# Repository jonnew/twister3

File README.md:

# Twister3
Twister3 is a simple and fast microwire twister from the [Wilson
Lab](http://web.mit.edu/wilsonlab/) at MIT. It is used to make tetrodes and
stereotrodes for invasive neural recordings. It can be purchased from the 
[Open Ephys store](https://open-ephys.org/twister-3).

### Documentation
Construction, usage, and performance information is provided in the [Twister3
manuscript](https://www.biorxiv.org/content/10.1101/727644v1). Please cite 
this paper if you use Twister3 in your research. If you have further questions, 
please direct them toward the [Open Ephys forum](https://groups.google.com/forum/#!forum/open-ephys).

### Licensing
Copyright Jonathan P. Newman & Jakob Voigts 2020

<br />This work is licensed under a <a rel="license" href="http://creativecommons.org/licenses/by-nc-sa/3.0/igo/">Creative Commons Attribution-NonCommercial-ShareAlike 3.0 IGO License</a>.

If your are interested in obtaining a license to sell this device, please contact us at https://open-ephys.org/contact

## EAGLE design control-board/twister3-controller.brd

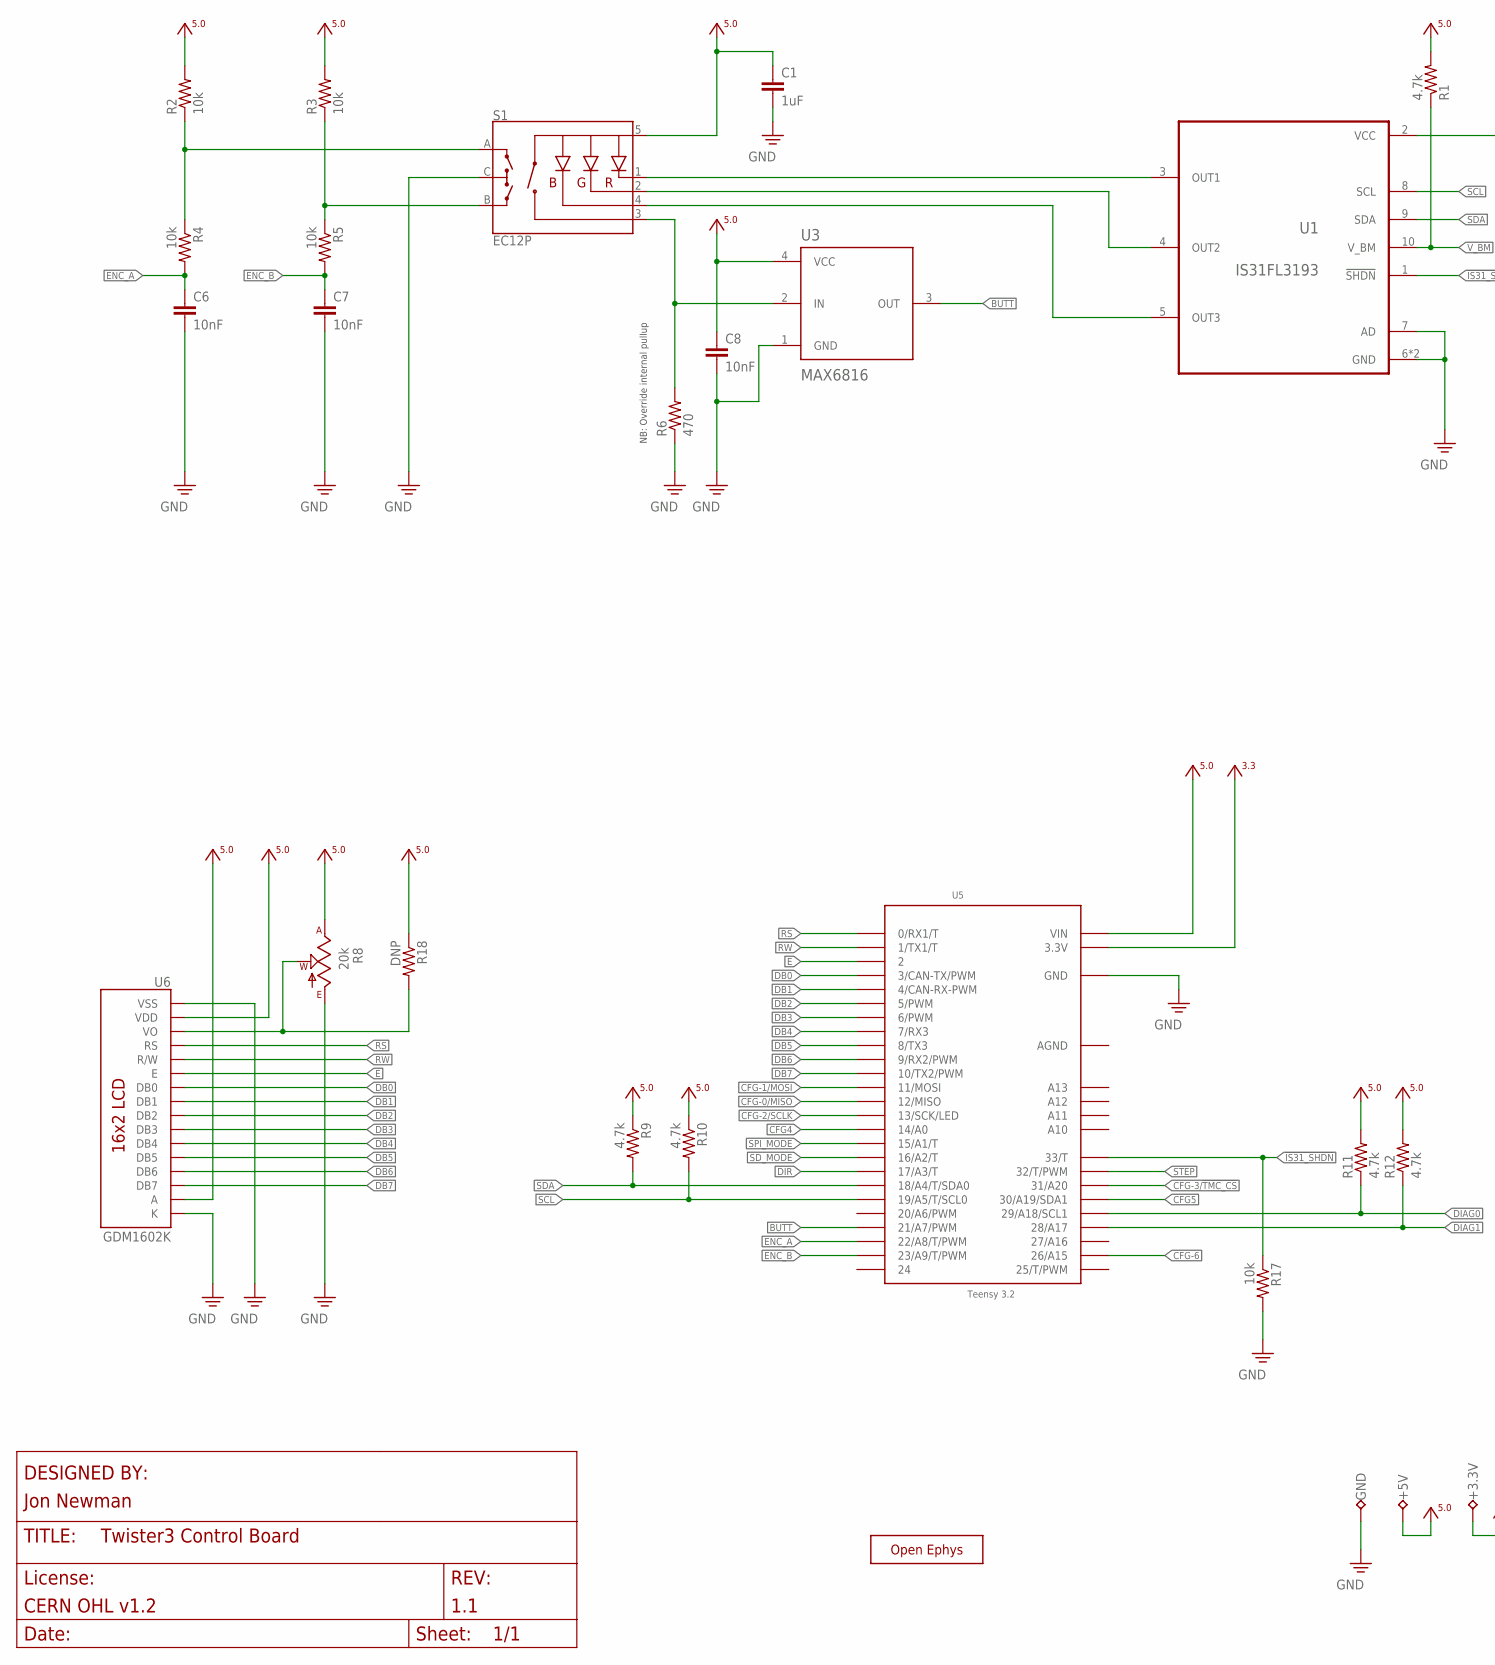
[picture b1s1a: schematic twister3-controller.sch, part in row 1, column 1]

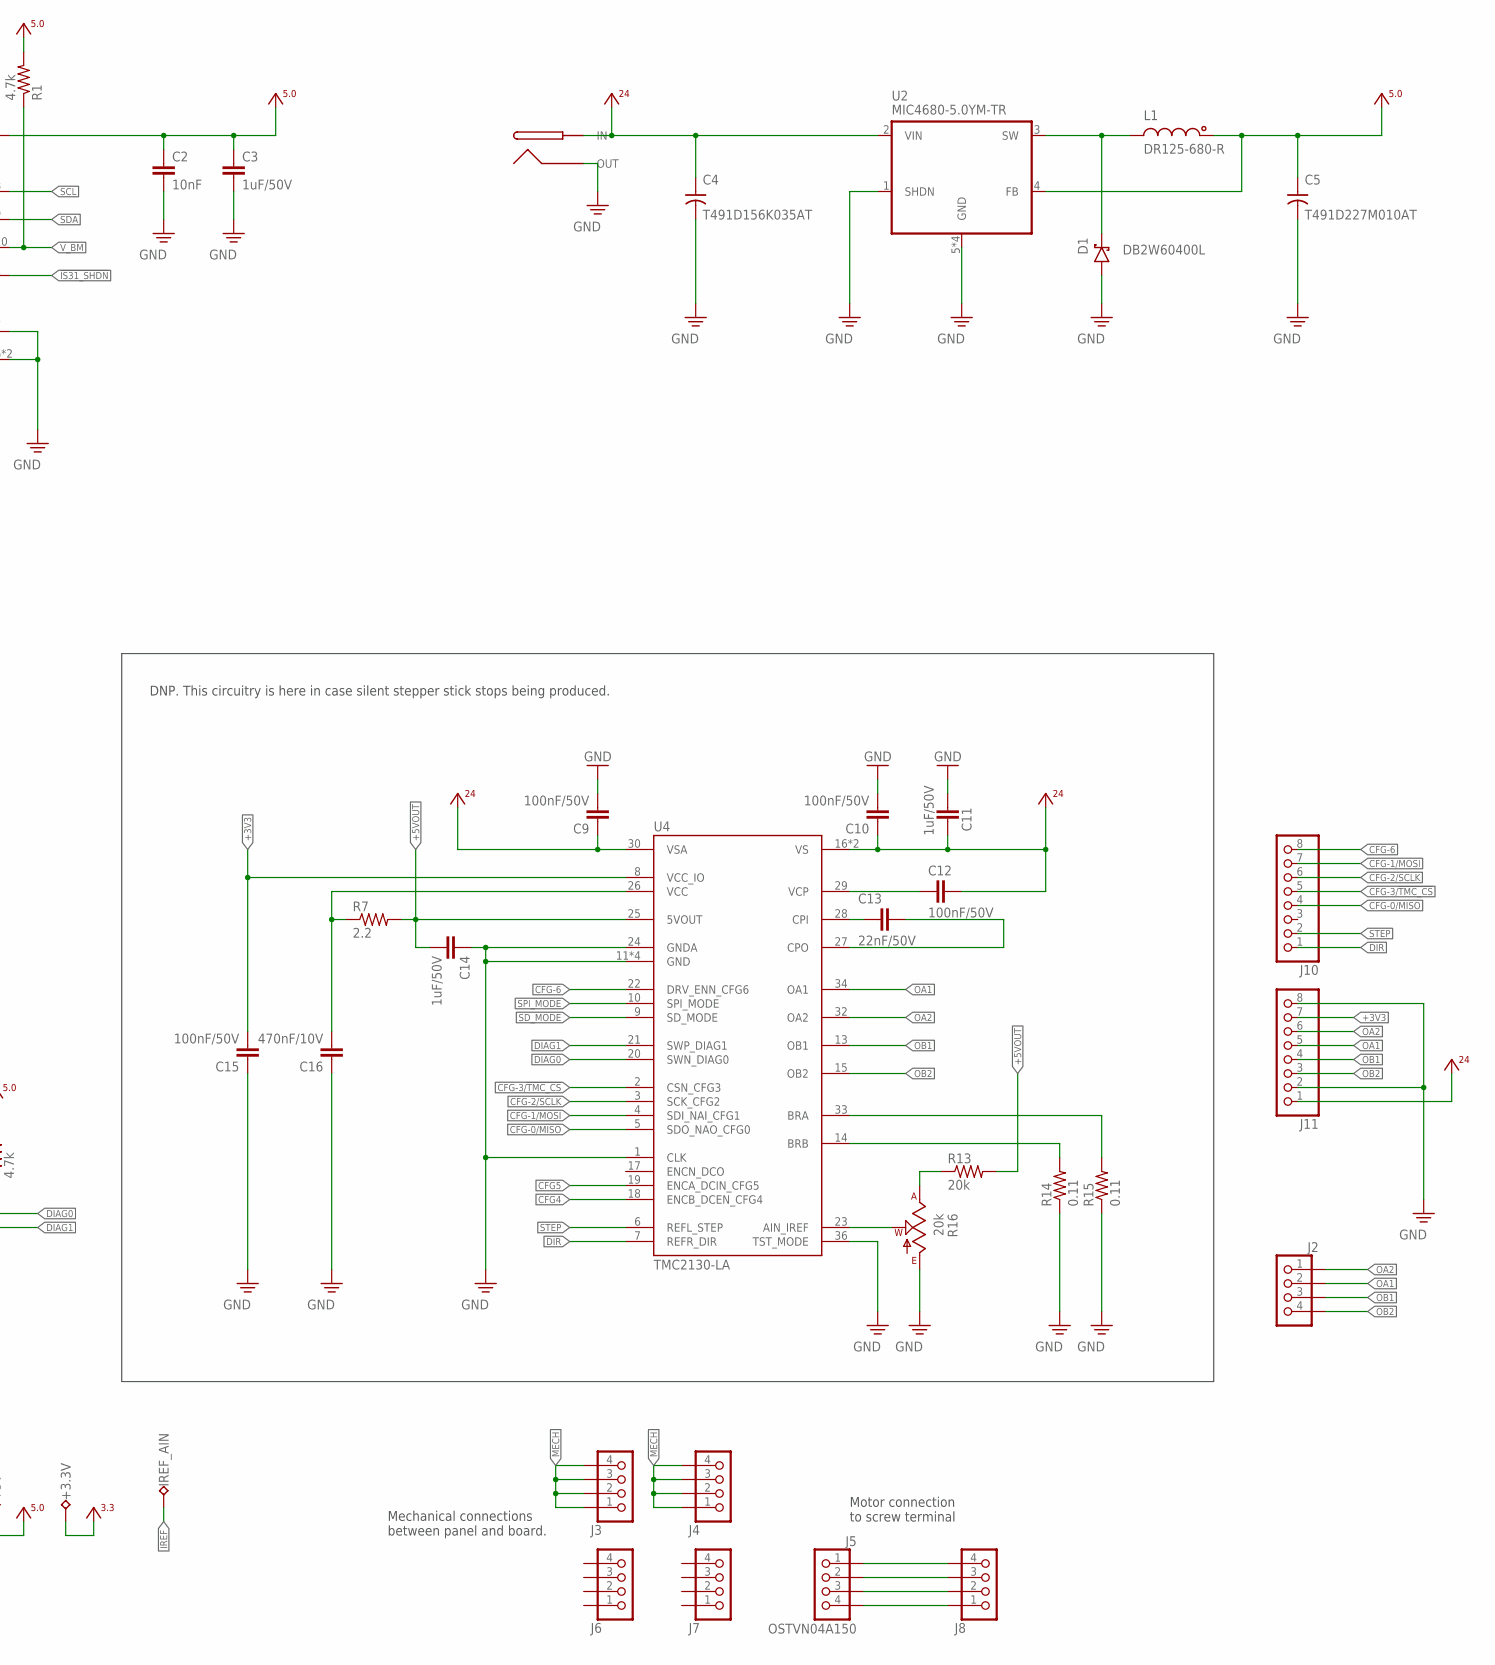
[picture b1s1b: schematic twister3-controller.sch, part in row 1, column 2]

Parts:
+3.3V, +5V: TP_2MM; TESTPOINT_2MM
C1: 1uF; 0603
C2, C6, C7, C8: 10nF; 0603
C3, C11, C14: 1uF/50V; 0603
C4: T491D156K035AT; 7343M
C5: T491D227M010AT; 7343M
C9, C10, C12, C15: 100nF/50V; 0603
C13: 22nF/50V; 0402
C16: 470nF/10V; 0402
D1: DB2W60400L; SOD123
GND: TP_2MM; TESTPOINT_2MM
IREF_AIN: TP_2MM; TESTPOINT_2MM
J1: BARREL-JACK_PJ-063BH; PJ-063BH
J2, J6, J7: PINHD-1X4; 1X04
J3, J4, J8: PINHD-1X4_SMD-0.1"; JP4_SMD
J5: OSTVN04A150; 1X04
J10, J11: PINHD-1X08_2.54-S; 1X08-S
L1: DR125-680-R; DR125
R1, R9, R10, R11, R12: 4.7k; 0603
R2, R3, R4, R5, R17: 10k; 0603
R6: 470; 0603
R7: 2.2; 0402
R8, R16: 20k; SM-42/43X
R13: 20k; 0603
R14, R15: 0.11; 0805
R18: DNP; 0603
S1: EC12P; ENCODER_LED_3
U1: IS31FL3193; PWSON-N10-3X3
U2: MIC4680-5.0YM-TR; SOIC127P500X400-8N
U3: MAX6816; SOT143-4
U4: TMC2130-LA; QFN36-PAD
U5: Teensy 3.2; TEENSY_3.1_CYCLOPS
U6: GDM1602K; LCD-16X2
X1: OE-LOGO_14X10; OE-LOGO-14X10

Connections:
!IS31_SHDN: R17.1, U1.1 (!SHDN), U5.33 (33/T)
+3V3: +3.3V.1, C15.2, J11.7, U4.8 (VCC_IO), U5.3.3V, U5.3.3V2 (3.3V)
+5V0: +5V.1, C1.1, C2.1, C3.1, C5.+, C8.1, L1.1, R1.2, R2.2, R3.2, R8.1 (A), R9.1, R10.1, R11.2, R12.2, R18.1, S1.5 (+), U1.2 (VCC), U2.4 (FB), U3.4 (VCC), U5.VIN, U6.2 (VDD), U6.15 (A)
+5VOUT: C14.2, R7.2, R13.2, U4.25 (5VOUT)
+24V0: C4.+, C9.1, C10.1, C11.1, C12.1, J1.1 (IN), J11.1, U2.2 (VIN), U4.16 (VS), U4.30 (VSA), U4.31 (VS)
AGND: U5.AGND
BRA1: R15.2, U4.33 (BRA)
BRB1: R14.2, U4.14 (BRB)
BUTT: U3.3 (OUT), U5.21/A7 (21/A7/PWM)
CFG4: U4.18 (ENCB_DCEN_CFG4), U5.14/A0
CFG5: U4.19 (ENCA_DCIN_CFG5), U5.30 (30/A19/SDA1)
CFG-0/MISO: J10.4, U4.5 (SDO_NAO_CFG0), U5.12 (12/MISO)
CFG-1/MOSI: J10.7, U4.4 (SDI_NAI_CFG1), U5.11 (11/MOSI)
CFG-2/SCLK: J10.6, U4.3 (SCK_CFG2), U5.13 (13/SCK/LED)
CFG-3/!TMC_CS: J10.5, U4.2 (CSN_CFG3), U5.31 (31/A20)
CFG-6: J10.8, U4.22 (DRV_ENN_CFG6), U5.26 (26/A15)
CPI1: C13.2, U4.28 (CPI)
CPO1: C13.1, U4.27 (CPO)
DB0: U5.3 (3/CAN-TX/PWM), U6.7 (DB0)
DB1: U5.4 (4/CAN-RX-PWM), U6.8 (DB1)
DB2: U5.5 (5/PWM), U6.9 (DB2)
DB3: U5.6 (6/PWM), U6.10 (DB3)
DB4: U5.7 (7/RX3), U6.11 (DB4)
DB5: U5.8 (8/TX3), U6.12 (DB5)
DB6: U5.9 (9/RX2/PWM), U6.13 (DB6)
DB7: U5.10 (10/TX2/PWM), U6.14 (DB7)
DIAG0: R11.1, U4.20 (SWN_DIAG0), U5.29 (29/A18/SCL1)
DIAG1: R12.1, U4.21 (SWP_DIAG1), U5.28 (28/A17)
DIR: J10.1, U4.7 (REFR_DIR), U5.17/A3 (17/A3/T)
E: U5.2, U6.6 (E)
ENC_A: C6.1, R4.2, U5.22/A8 (22/A8/T/PWM)
ENC_B: C7.1, R5.2, U5.23/A9 (23/A9/T/PWM)
GND: C1.2, C2.2, C3.2, C4.-, C5.-, C6.2, C7.2, C8.2, C9.2, C10.2, C11.2, C14.1, C15.1, C16.1, D1.A, GND.1, J1.2 (OUT), J11.2, J11.8, R6.1, R8.3 (E), R14.1, R15.1, R16.3 (E), R17.2, S1.C, U1.6 (GND), U1.7 (AD), U1.PAD (GND), U2.1 (SHDN), U2.5 (GND), U2.6 (GND), U2.7 (GND), U2.8 (GND), U3.1 (GND), U4.1 (CLK), U4.11 (GND), U4.12 (GND), U4.24 (GNDA), U4.35 (GND), U4.36 (TST_MODE), U4.TP (GND), U5.GND, U5.GND2 (GND), U6.1 (VSS), U6.16 (K)
IREF: IREF_AIN.1, R16.2 (W), U4.23 (AIN_IREF)
MECH: J3.1, J3.2, J3.3, J3.4, J4.1, J4.2, J4.3, J4.4
unnamed: R2.1, R4.1, S1.A
unnamed: R6.2, S1.3 (SW), U3.2 (IN)
unnamed: S1.1 (-R), U1.3 (OUT1)
unnamed: R3.1, R5.1, S1.B
unnamed: J5.1, J8.4
unnamed: J5.2, J8.3
unnamed: J5.3, J8.2
unnamed: J5.4, J8.1
unnamed: S1.2 (-G), U1.4 (OUT2)
unnamed: R8.2 (W), R18.2, U6.3 (VO)
OA1: J2.2, J11.5, U4.34 (OA1)
OA2: J2.1, J11.6, U4.32 (OA2)
OB1: J2.3, J11.4, U4.13 (OB1)
OB2: J2.4, J11.3, U4.15 (OB2)
RS: U5.0 (0/RX1/T), U6.4 (RS)
RW: U5.1 (1/TX1/T), U6.5 (R/W)
SCL: R10.2, U1.8 (SCL), U5.19/A5 (19/A5/T/SCL0)
SDA: R9.2, U1.9 (SDA), U5.18/A4 (18/A4/T/SDA0)
SD_MODE: U4.9 (SD_MODE), U5.16/A2 (16/A2/T)
SPI_MODE: U4.10 (SPI_MODE), U5.15/A1 (15/A1/T)
STEP: J10.2, U4.6 (REFL_STEP), U5.32 (32/T/PWM)
SUPPY4: S1.4 (-B), U1.5 (OUT3)
SW: D1.C, L1.2, U2.3 (SW)
VCC1: C16.2, R7.1, U4.26 (VCC)
VCP1: C12.2, U4.29 (VCP)
VREF2: R13.1, R16.1 (A)
V_BM: R1.1, U1.10 (V_BM)

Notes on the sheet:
NB: Override internal pullup
Mechanical connections between panel and board.
Motor connection to screw terminal
DNP. This circuitry is here in case silent stepper stick stops being produced.

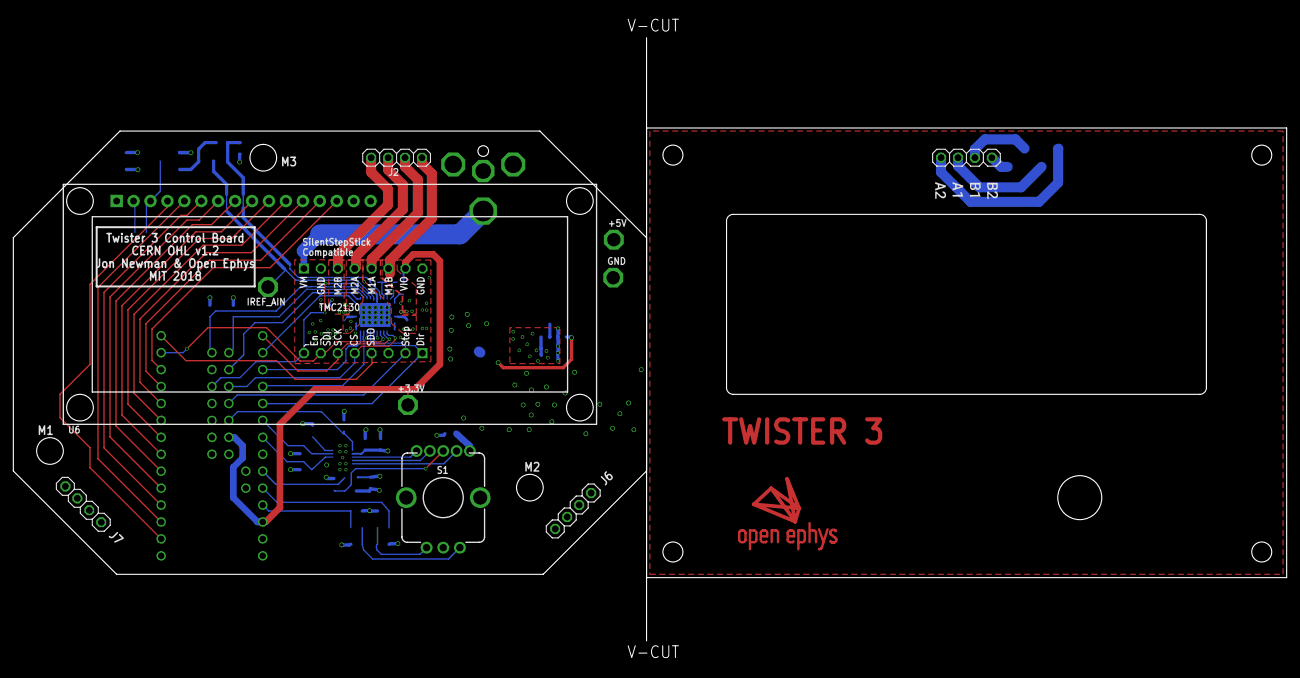
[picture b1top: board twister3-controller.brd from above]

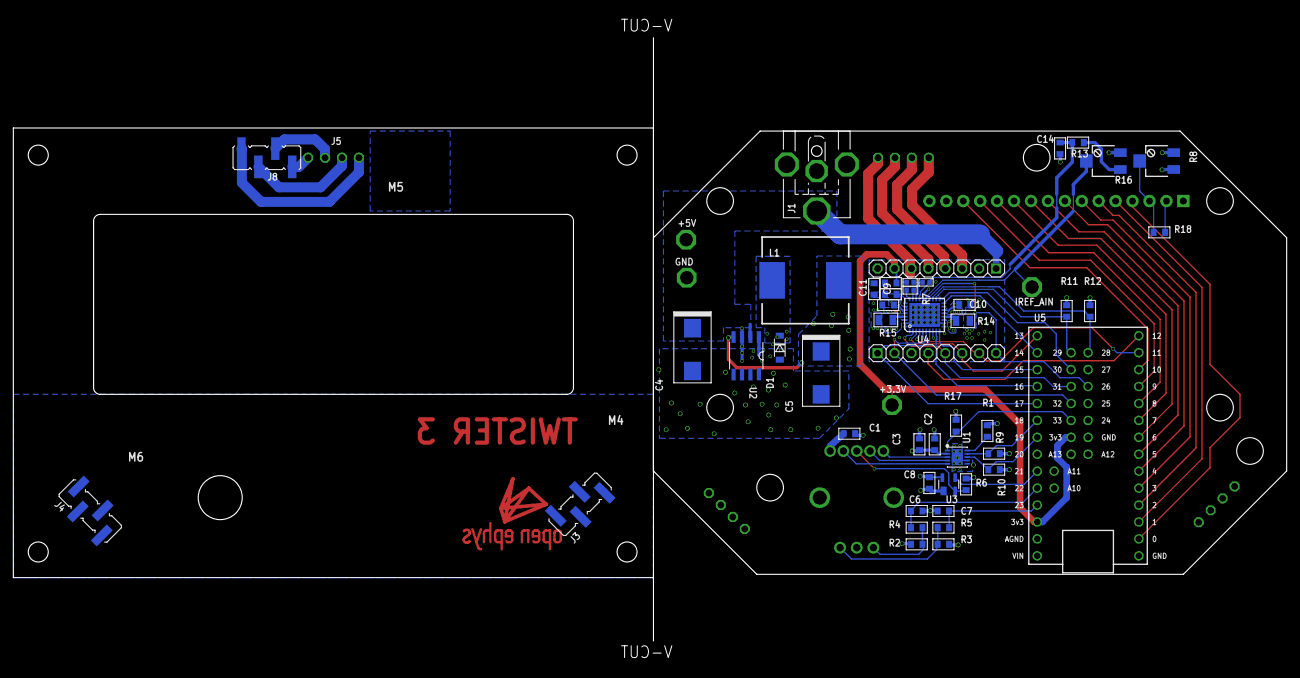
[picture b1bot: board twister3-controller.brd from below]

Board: 4 copper layers, 191.0 x 90.5 mm, 58 parts (47 on the bottom side), 61 nets.

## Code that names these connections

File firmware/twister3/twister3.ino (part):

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
// RGB Driver
#define IS31_ADDR 0x68
#define IS31_SHDN 33

// Rotary encoder pins
#define ENC_A 22
#define ENC_B 23
#define ENC_BUTT 21

// Settings address start byte.
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    Wire.setDefaultTimeout(200000); // 200ms

    // Enable LED current driver
    pinMode(IS31_SHDN, OUTPUT);
    digitalWriteFast(IS31_SHDN, HIGH);
    delay(1);

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
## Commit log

2017-11-23 Initial commit.
2017-11-29 TT spool portion of twister
    - 4 pre-loaded TT bobins on adjustable post
2017-11-30 Finished basic mechanical components
    - Added motor mounts, spinning mechanism, and spool loading adapters
    - Twister3.sldasm has the complete assembly
2017-12-01 Addressed Jakob's comments
    - The comments are shown here
    - All are addressed but I opted to keep the screws holding the bearings
    instead of using dowels
    you got a few missing components there that are not in the right path
    the loading stepper motor holder looks odd instead of compressing with
    set screws i would screw the motor into a adapter plate from below or
2017-12-02 Final touches before first fabrication iteration
    - 3D parts off to printers
    - Ordering TL and MMC parts
2018-01-02 Updates to deal with unstable spinning in rev 1.0
    - Larger moment of inertia in hanger
    - Other minor fixes
2018-01-04 Added 3d printed spring-loaded spinning base
    we'll likely want to try a few different thicknesses/spring constants
2018-01-05 added 2nd spring clip holder variant
2018-02-26 Revisions after using prototype pretty extensively
    - Major design simplification
    - All attachment at motor is done by alignment pin + magnets
    - Bobbins are larger and have flat channels for TT wire
    - Bobbins are held to spinner via magnets for loading
    - The hanging spinners have been removed because they dont work
    - The non-functional leaf-spring spinners have been removed
2018-02-26 Added README and reorganized repo
    - Now that the thing is working, should clean up a bit.
2018-03-01 Added primitive firmware for controller.
2018-03-05 Fixed mode selections issues
    - Very hacky solution
    - Also fixed screen constantly updating without needing to
    - Added feature that saves settings to EEPROM every turn
2018-04-17 Started twister3 control board
    - Schematic is not finished
    - Basically a mashup of teensy, rotary encoder knob, debounce IC, silent
    stepper stick.
    - Idea is to keep silent stepper stick form factor so that you can
    either plug one in or populate the board when the become obsolete
2018-07-04 Pretty much done with r1.0 of control board
    - Stacking PCB design
    - Top PCB is a panel that fits into a plastic enclosure
    - Bottom holds electronics (Teensy 3.2, LCD, motor driver, encoder, etc)
    - 0.1" headers hold the two boards together
    - I'm trying to use hacked GND press clips to clip the LCD PCB to the
    panel board instead of screws/standoffs. The goal is the two PCBs should
2018-07-09 Updates to cad and README
    - Improved bobbin base. Use a hex standoff instead of tapping M3s right
    into plastic
    - Improved wire guide.
    - Other small CAD changes
    - Added to README. e.g. put links to BOM
2018-07-11 Complete rev 1.0 of control board
    - Off to fab
2018-07-24 Made arm-base hex insert slightly bigger
    - Press fit was a bit intense
    - STL updated and uploaded to shapeways
2018-08-08 Minor edits to MANUAL.txt
    - Refined sections a bit
    - Added Makefile to create PDF
2018-08-09 Update firmware for control board rev. 1.0
    - Control of RGB LED
    - Remove manual debounce since board has debouce IC
    - Change to quadrature encoder
    - Etc
2018-08-09 Updated control board after assembly
    - Removed redudant mechanical connectors
    - Added positions for SMD nuts on bottom of panel board
    - Replace most 0805 components with 0603
    - Other minor changes
2018-08-11 Small updates to control board
    - Tighter tolerance on LCD cutout
    - Added test points
2018-08-26 CAD up to date for creation of manual
    - Added different display states etc that will result in figures for the
    manual
2018-08-26 Adding resources for manual derived from CAD
    - Assembly and operation steps
    - Incomplete
2018-08-27 Convert binary files to git LFS
    - Some updates to resources
    - Added control box usage figure
2018-09-04 Updates to control board after assembly of rev 1.1
    - Better retaining mechanism for top panel
    - Simplified and updated BOM on the google doc to match this version
2019-01-21 Some work on MANUAL.txt
    - Added missing MANUAL.pdf
    - Updated some contruction steps
2019-02-20 Minor clarifying updates to MANUAL and schematic
2019-02-20 Added initial paper progress
2019-02-21 Added design-features figure
2019-02-21 Modified wire guide s.t. it gets closer to bobbin
    - Wire guide can now extend over motor mount so that wire can be cleanly
    feed onto the bobbin during loading
2019-02-21 Improved design-features figure.
2019-02-22 Added overview of mechanics to figure 1.
2019-02-23 Added figure of block-level electronics for paper
    - Image of control box has been doctored with gimp to get rid of the pot
    adjustment holes and reset switch, which will be removed for production
2019-02-23 Removed trimpot access in control board front panel
    - Trimpots should be set during assembly and glued, access is not
    required during operaiton. Also, current trimpot only works if the
    silent stepper stick module is not used with is not the default case.
    - Also, removed reset switch (since this can be done by removing
    power...)
2019-02-23 Some minor updates to MANUAL.*
    - Also updated control board schematic to indicate that stepper driver
    circuit should not be populated if you are using a silent stepper stick.
    - At this point, I'm considering the MANUAL deprecated and moving its
    contents to the paper, which will act as a manual when it is finished.
2019-02-24 Lots of edits and progress to twister3.tex
    - Also, added mechanical and 3d prining BOM tables
2019-02-25 Added assembly steps for mechanical components to paper
    - Along with a lot of other text that is taken from the MANUAL
2019-02-27 Added other-assembly figure and modified other figures
    - Reorganized files
    - Eventually merge paper with resources folder
2019-02-27 Standardized figure size and font
    - All figures 170mm width and fonts standardized
    - No scaling needed for A4 paper
2019-02-27 Added twister3 assembly steps figure
2019-02-27 Update cad with views and simulations for paper
    - Simulation of leaf spring deformation
    - Assemblies have lots of alternative views for figures in paper
2019-02-27 Add usage figure for paper
    - Instructions for loadinb bobbins and twisting tetrodes
2019-02-28 Added usage figure to text
    - Update author affiliations
    - Added emails with spike gadgets folks as seed for dicussion section
2019-02-28 Added tetrode alignment attachment to spring top
    - Slots in over magnet and alings wire bundle with turn axis
2019-03-03 Added references to paper
    - Wrote most of discussion
    - Other small edits
    - Need to measure probe stifness, show plating characterisitcs, and some
    example recordings
    - Need to add alignment clip to figures and show a zoom in of how it
    works
2019-03-04 Added little hands to usage figure
2019-03-12 Made rotor base alignment pin longer
    - Jakob was complaining that he could knock bobbins off during reloading
2019-03-22 Updates to parts during final testing
    - Compensated for leaf-spring manufacturing process
    - Add threads to motor base
    - Relieve magnets by .25 mm
2019-04-02 Added TT mechanical measurements figure
    - Also added script that generates it which contains raw data
2019-04-02 Update tt mechanical properties figure
2019-04-04 Corrected tt mechanics figure
    - Stiffness plot is vs L not delta L
2019-04-04 Update script for new tt mechanical properties plot.
2019-04-30 Fixes to figures to include wire aligner
    - The usage figure still needs to be updated
2019-04-30 Updates to figures to include wire aligner
    - Updates to CAD to get these figures
    - Usage figure is now up to date
2019-04-30 Update usage figure to show more steps
    - Added spinning, loosening, and cutting steps
2019-05-01 Update usage figure to include fusing step
2019-05-06 Splite spring mount into two alignment pieces
    - The center of rotation of the leaf spring can now be adjusted to match
    the motor axis. This is to account for imperfections in 3D printing and
    offsets due to spring action
2019-05-06 Added tetrode making time measurements
2019-05-08 Made stls for rotor alignment parts
    - Added thumbscrews for the feeder screws
2019-05-17 Updated firmware for new version of TeensyStep
    - Inclued all library dependencies that dont ship with Arduino or
    Teensyduino in the libraries folder
2019-05-31 Additional measurements added to paper
    - Leaf spring constant
    - Motor in motion time
    - Etc
2019-06-01 Update paper figures with new alignment mechanism
    - CAD also up to date
2019-06-01 Started added example trace to tt-mech figure
2019-06-02 Nearly complete first draft
    - I'm sending this out to authors for review before going further
2019-07-15 Added image of thumbwheel.
2019-07-15 Added tt data and plotting scripts
    - Example tetrode data from rat and mouse courtesy of Hector Penagos
2019-07-15 Address Ming's comments in the figures
    - Added thumwheel
    - Fixed issues in labelling inconsistencies
    - Added mouse and rat tt data to tt-mech figure
2019-07-16 Final updates to manuscript before sending to co-authors
    - Small BOM fixes
    - Address the mouse and rat recordings in main text
    - Finish adding open source project examples to discussion
2019-07-17 Repo cleanup before paper finalization
    - Removed defunct manual
    - Moved all relevant resources to paper directory
    - Update README with current documenation pointers
    - Small paper organization mods
2019-07-17 Added board fabrication information
2019-07-18 Small fixes to figures
2019-07-18 Update manuscripts with notes from Jakob
2019-08-06 Final edits to paper before bioarxiv submission
    - Fixed mech bom
    - Added open ephys affiliation
2019-08-07 Add bioarxiv link to README
2019-09-18 Added cut in side of wire guide
    - This allows the wire to be loaded much easier instead of having to
    thread it through the guide
2020-01-05 Updates to control board for OEPs production
    - Increase hole tolerances
    - Decrease via size in thermal pads to prevent solder voiding
    - Added stencil files
2020-01-05 Added missing files from last commit
2020-01-06 Added oe-logo and Twister 3 to tstop on front panel
    - Reduced the both bcream and bstop for the SMD threaded inserts to 3.2
    mm on bottom on front panel
2020-01-09 Move potentiometers to bottom of board
    - This will cut down on production costs since they are not available
    through the front panel anyway
    - Alternative, hard-coded resistor (not populated) for LCD bias
2020-01-27 Modified figures in accordance with reviewer requests
    - Insets in usage figure increased in size 2x
    - Add tungsten mechanical measurements
    - Add images of TT shafts
2020-02-07 Finished addressing reiewer comments on paper
    - Ready for resbumission
2020-06-19 Created custom enclosure for the motor controller
    - Bottom PCB is snap in
    - Automatic supports for LCD
    - Top PCB requires 4 M3 screws and these hold the whole assembly
    together
2020-06-20 Fixed asymmetric pcb placement in control-box encolsure
    - Hole placement was a bit off center resulting in asymmetic tolerances
    on the sides of the enclosure
    - Supressed snap in tabs per Filipe's request
2020-06-24 Reduced the depth of the controller enclosure by 2.75 mm
    - Attempting to reduce cost
2020-07-26 Replaced CERN OHL with CC BY-SA-NC
2020-07-26 Fixed shifted power input hole on the 3D printed controller case
    - It was improperly offset from the side
2022-05-30 Update README.md
    - Add link to store

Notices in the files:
control-board/twister3-controller.brd:
CERN OHL v1.2
control-board/twister3-controller.sch:
LICENSE: CERN OHL v1.2
parts and their libraries:
SparkFun-Switches: Licensing: Creative Commons ShareAlike 4.0 International - https://creativecommons.org/licenses/by-sa/4.0
